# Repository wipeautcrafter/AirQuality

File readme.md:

# Air Quality Monitor
An open-source IOT air quality monitor measuring Temperature, Humidity and CO2 PPM.

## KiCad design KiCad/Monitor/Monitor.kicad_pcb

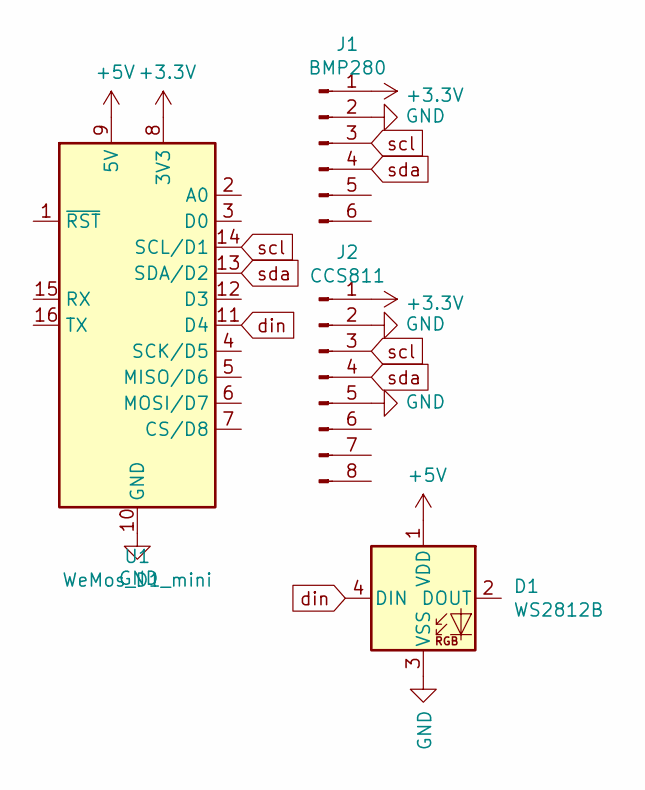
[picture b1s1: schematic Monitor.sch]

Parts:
D1: WS2812B; LED_WS2812B_PLCC4_5.0x5.0mm_P3.2mm
J1: BMP280
J2: CCS811
U1: WeMos_D1_mini; WEMOS_D1_mini_light

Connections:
+3V3: J1.1, J2.1, U1.8 (3V3)
+5V: D1.1 (VDD), U1.9 (5V)
GND: D1.3 (VSS), J1.2, J2.2, J2.5, U1.10 (GND)
din: D1.4 (DIN), U1.11 (D4)
scl: J1.3, J2.3, U1.14 (SCL/D1)
sda: J1.4, J2.4, U1.13 (SDA/D2)

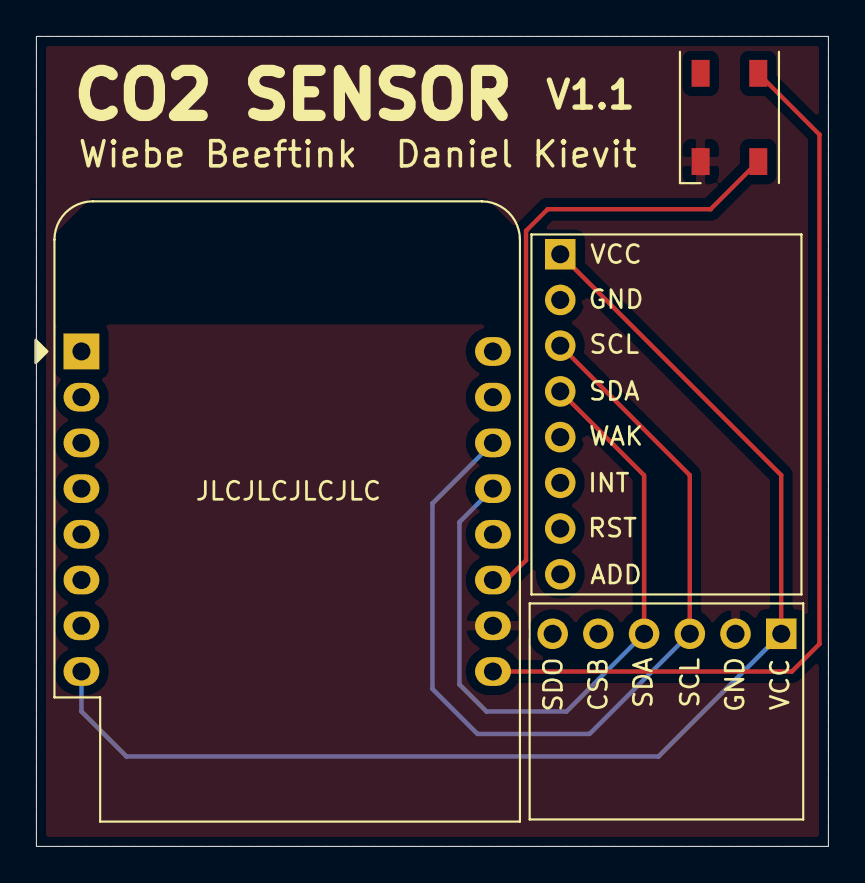
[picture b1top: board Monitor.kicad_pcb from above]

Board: 2 copper layers, 44.0 x 45.0 mm, 4 parts (0 on the bottom side), 6 nets.

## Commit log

2021-05-28 added kicad files
2021-05-29 first design
2021-05-29 fixed pcb
2021-06-10 v1.1
2021-06-10 removed gerber files
2021-06-26 test sensor
2021-09-05 added logging
2021-09-05 added dockerfile
2021-09-05 added start script
2021-09-05 removed run
2021-09-05 removed log
2021-09-29 made initial version of site
2021-12-03 sensor ino
